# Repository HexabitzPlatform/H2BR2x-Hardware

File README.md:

# H2BR2x-Hardware
Hexabitz Galvanic-Skin-Response Monitor Module Hardware Design

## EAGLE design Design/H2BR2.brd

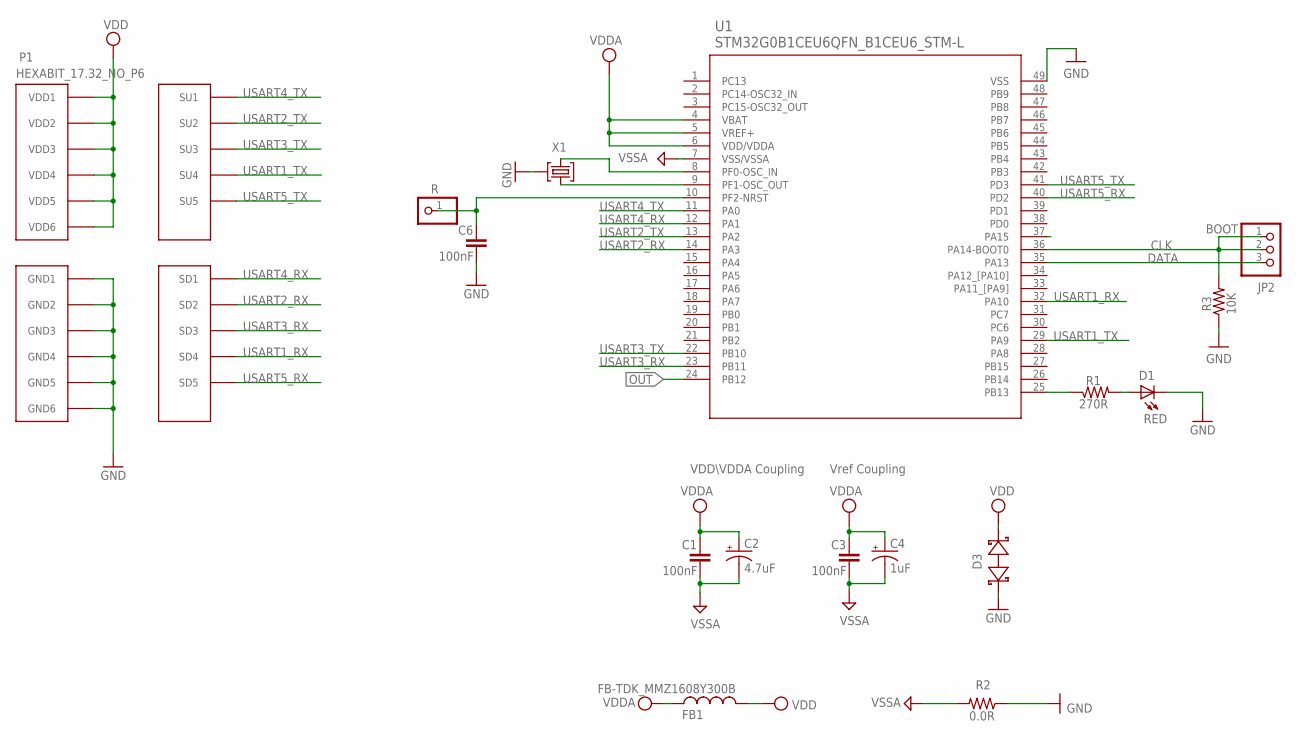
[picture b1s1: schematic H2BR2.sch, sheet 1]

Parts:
C1, C3, C6: 100nF; C-0603
C2: 4.7uF; C-0805-POL
C4: 1uF; C-0805-POL
D1: RED; VLMS1300-GS08; MPN VLMS1300-GS08
D3: BOURNS_CDSOD323-T03SCBOURNS_CDSOD323-T03SC_0_0; BOURNS_CDSOD323-T03SC_0
FB1: FB-TDK_MMZ1608Y300B; FB-0603; MPN MMZ1608Y300B
JP1: R; 1X01
JP2: PINHD-1X3; 1X03
P1: HEXABIT_17.32_NO_P6
R1: 270R; R-0603
R2: 0.0R; R-0603; MPN RC0603JR-070RL
R3: 10K; R-0603
TRIMBLE-LOGO1: HEXA-LOGO
U1: STM32G0B1CEU6QFN_B1CEU6_STM-L; QFN_B1CEU6_STM-L
X1: XTALL_CSTCE8M00G52

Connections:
CLK: JP2.1, JP2.2, R3.2, U1.36 (PA14-BOOT0)
DATA: JP2.3, U1.35 (PA13)
GND: C6.2, D1.C, D3.1 (A), P1.PAD_PD7 (GND1), P1.PAD_PD8 (GND2), P1.PAD_PD9 (GND3), P1.PAD_PD10 (GND4), P1.PAD_PD11 (GND5), P1.PAD_PD12 (GND6), R2.1, R3.1, U1.49 (VSS), X1.P$2 (2); also elsewhere on the board
unnamed: R1.1, U1.25 (PB13)
unnamed: D1.A, R1.2
unnamed: C6.1, JP1.1, U1.10 (PF2-NRST)
unnamed: U1.9 (PF1-OSC_OUT), X1.P$1 (1)
unnamed: U1.8 (PF0-OSC_IN), X1.P$3 (3)
OUT: U1.24 (PB12); also elsewhere on the board
USART1_RX: P1.PAD_PD4 (SD4), U1.32 (PA10)
USART1_TX: P1.PAD_PU4 (SU4), U1.29 (PA9)
USART2_RX: P1.PAD_PD2 (SD2), U1.14 (PA3)
USART2_TX: P1.PAD_PU2 (SU2), U1.13 (PA2)
USART3_RX: P1.PAD_PD3 (SD3), U1.23 (PB11)
USART3_TX: P1.PAD_PU3 (SU3), U1.22 (PB10)
USART4_RX: P1.PAD_PD1 (SD1), U1.12 (PA1)
USART4_TX: P1.PAD_PU1 (SU1), U1.11 (PA0)
USART5_RX: P1.PAD_PD5 (SD5), U1.40 (PD2)
USART5_TX: P1.PAD_PU5 (SU5), U1.41 (PD3)
VDD: D3.2 (C), FB1.2, P1.PAD_PU7 (VDD1), P1.PAD_PU8 (VDD2), P1.PAD_PU9 (VDD3), P1.PAD_PU10 (VDD4), P1.PAD_PU11 (VDD5), P1.PAD_PU12 (VDD6); also elsewhere on the board
VDDA: C1.1, C2.1 (+), C3.1, C4.1 (+), FB1.1, U1.4 (VBAT), U1.5 (VREF+), U1.6 (VDD/VDDA)
VSSA: C1.2, C2.2 (-), C3.2, C4.2 (-), R2.2, U1.7 (VSS/VSSA)

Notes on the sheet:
Vref Coupling
VDD\VDDA Coupling
BOOT

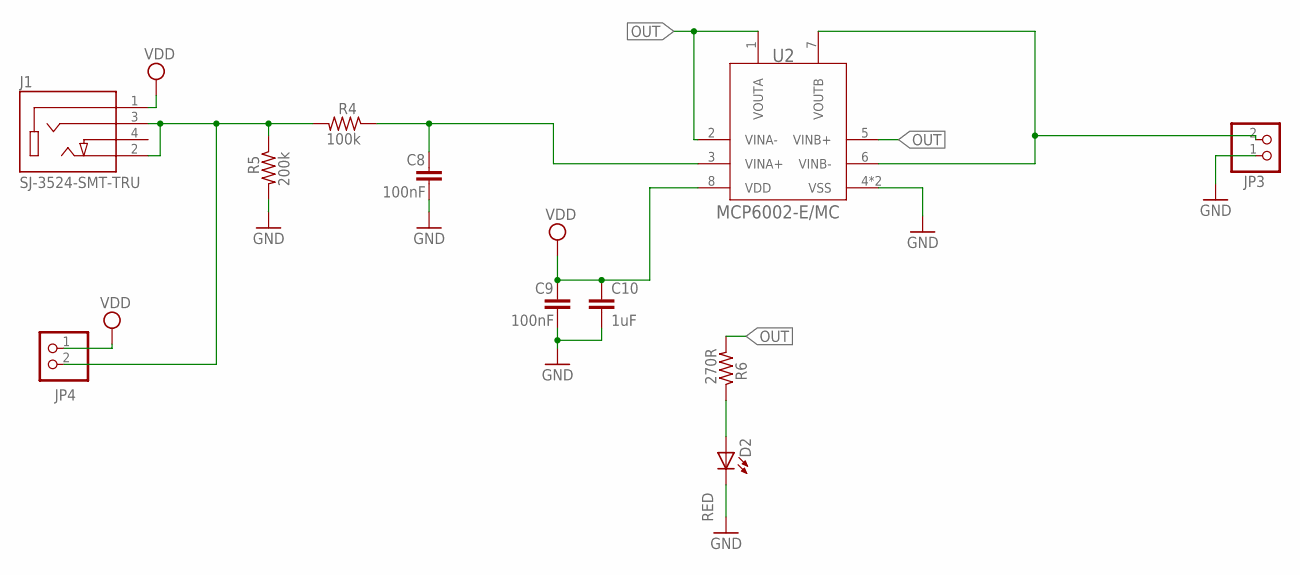
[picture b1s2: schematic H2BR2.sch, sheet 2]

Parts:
C8, C9: 100nF; C-0603
C10: 1uF; C-0805
D2: RED; VLMS1300-GS08; MPN VLMS1300-GS08
J1: SJ-3524-SMT-TRU; CUI_SJ-3524-SMT
JP3, JP4: PINHD-1X2(ROUND); 1X02
R4: 100k; R-0603
R5: 200k; R-0603
R6: 270R; R-0603
U2: MCP6002-E/MC; SON50P200X300X100-9N

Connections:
GND: C8.2, C9.2, C10.2, D2.C, JP3.1, R5.2, U2.4 (VSS), U2.9 (VSS); also elsewhere on the board
unnamed: JP3.2, U2.6 (VINB-), U2.7 (VOUTB)
unnamed: C8.1, R4.1, U2.3 (VINA+)
unnamed: J1.2, J1.3, JP4.2, R4.2, R5.1
unnamed: D2.A, R6.1
OUT: R6.2, U2.1 (VOUTA), U2.2 (VINA-), U2.5 (VINB+); also elsewhere on the board
VDD: C9.1, C10.1, J1.1, JP4.1, U2.8 (VDD); also elsewhere on the board

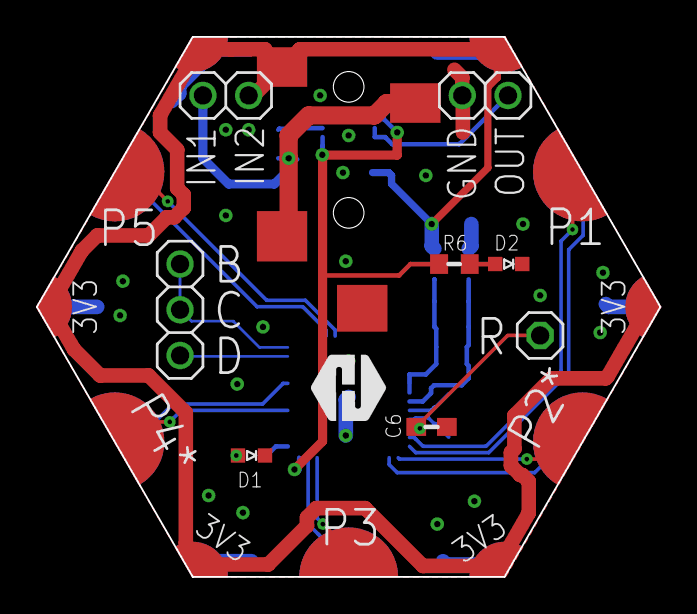
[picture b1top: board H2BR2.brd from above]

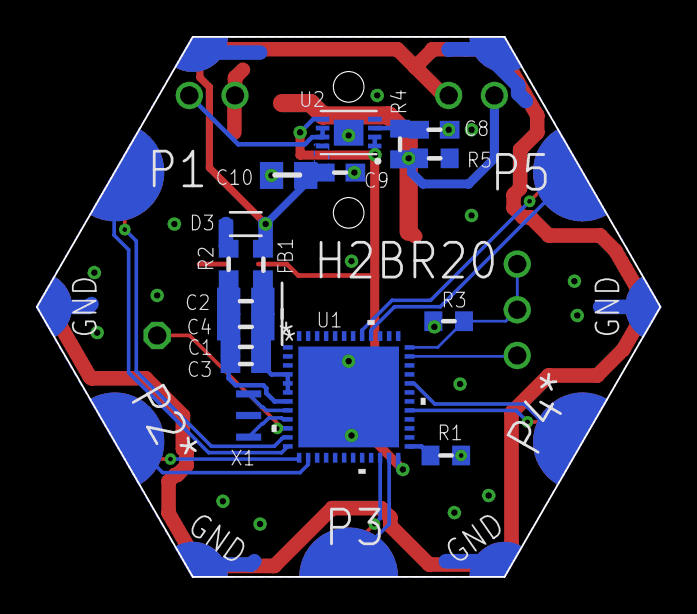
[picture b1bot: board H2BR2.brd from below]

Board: 2 copper layers, 34.6 x 30.0 mm, 28 parts (17 on the bottom side), 26 nets.

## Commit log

2024-12-21 -The final design, all done.
2024-12-25 Fix BOM file name

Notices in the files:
parts and their libraries:
COPYRIGHT: Copyright (C) 2021 Ultra Librarian. All rights reserved.
